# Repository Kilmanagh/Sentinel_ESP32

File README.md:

# Sentinel ESP32

Sentinel is an ESP32-based multi-sensor node built around ESPHome and Home Assistant.

The active implementation lives in `esphome/sentinel.yaml`. The old PlatformIO project in `pio-ARCHIVE/` is deprecated and is no longer the source of truth.

## Current firmware

- Active config: `esphome/sentinel.yaml`
- Secrets file: `esphome/secrets.yaml`
- Board target: `esp32dev`
- Framework: ESPHome on Arduino
- Home Assistant integration: native ESPHome API
- Device services: Wi-Fi, OTA, web server, local fallback AP, and Home Assistant entity-based runtime tuning

## Features

- BME280 environment telemetry
- AM312 PIR motion detection with warmup, stable-detect, stable-clear, and hold timing
- MAX9814 sound intrusion detection using peak-to-peak sampling
- Reed switch door state reporting
- Sound-level calibration helpers and approximate dB display
- Smoke alarm tone and cadence detection
- Device-health diagnostics and fault indicators
- Three-pixel WS2812 status LED strip plus onboard status LED
- Runtime tuning through Home Assistant entities exposed by ESPHome

## Primary docs

- `docs/Adjustments.MD` - active ESPHome tuning, calibration, and sensor-behavior guide
- `docs/Hardware_Deliverables.md` - current hardware, pin mapping, and LED wiring summary
- `hardware/Sentinel_Baseplate_Kit_Wiring.md` - practical baseplate / Dupont wiring guide for the actual 30-pin ESP32 board and expansion kit
- `hardware/Sentinel_Baseplate_Kit_Wiring.md` also includes a Sentinel-only pin map and a first bring-up checklist for bench validation
- `docs/Sentinel_Home_Assistant_Helpers.md` - optional Home Assistant helper package for counters, mode helpers, and last-event tracking
- `docs/Sentinel_Lovelace_Dashboard.md` - dashboard layout, setup, and troubleshooting view
- `docs/Sentinel_Lovelace_Dashboard.yaml` - Lovelace YAML for the dashboard itself

## Deploy

Use ESPHome to validate and install `esphome/sentinel.yaml`.

Typical workflow:

1. Fill in `esphome/secrets.yaml` with your Wi-Fi credentials.
2. Open `esphome/sentinel.yaml` in ESPHome or the Home Assistant ESPHome add-on.
3. Validate the config.
4. Install over USB for first flash, then use OTA afterward if desired.

## Notes

- The active docs no longer use the old MQTT, serial `cfg`, or BLE watchlist workflow.
- If you need historical PlatformIO material, keep it isolated under `pio-ARCHIVE/`.

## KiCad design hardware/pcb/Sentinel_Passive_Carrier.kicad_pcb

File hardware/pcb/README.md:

# PCB Package

This directory holds PCB fabrication package assets.

## Current recommendation

For the current Sentinel hardware build, do not treat this folder as the primary assembly path.

The recommended real-world build is:

- the existing AITRIP ESP32 baseplate / expansion kit
- Dupont wiring
- the practical wiring guide in `hardware/Sentinel_Baseplate_Kit_Wiring.md`

This `hardware/pcb/` folder should currently be treated as an experimental custom-board branch and documentation artifact, not the default build path.

## Current source

- `Sentinel_Passive_Carrier.kicad_pcb`: generated KiCad board source for a passive carrier board
- `generate_passive_carrier.py`: reproducible pcbnew generator for the current board source
- `Sentinel_Passive_Carrier_drc.rpt`: latest KiCad DRC report

## Current design scope

This is a passive carrier board derived from the current wiring, schematic, and enclosure documentation.

It assumes:

- ESP32 DevKit remains off-board and connects through a wire harness header rather than a direct socket footprint
- BME280, AM312, MAX9814, reed switch, and LED strip land on generic header / terminal positions
- board outline is sized conservatively to fit within the current 95 mm x 65 mm enclosure envelope

It is useful for:

- preserving the custom PCB experiment
- future routing / layout work
- exporting fabrication files for review while the design is still being corrected

It is not yet the recommended path for:

- immediate hardware assembly
- ordering production boards
- using as the single source of truth for the active build

## Fabrication package

The `gerbers/` folder now contains real KiCad exports for the passive carrier board, including:

- copper layers
- solder mask layers
- silkscreen layers
- edge cuts
- Excellon drill file
- drill map and drill report
- KiCad gerber job file

## Validation status

The fabrication package is generated from a real board source, but the current carrier layout is not yet fully DRC-clean.

Practical meaning:

- the files are real KiCad exports
- the board is still not ready to be treated as fabrication-safe
- the DRC report must be resolved before any board order is placed

Until that happens, the active hardware reference remains the baseplate / Dupont path documented in `hardware/Sentinel_Baseplate_Kit_Wiring.md`.

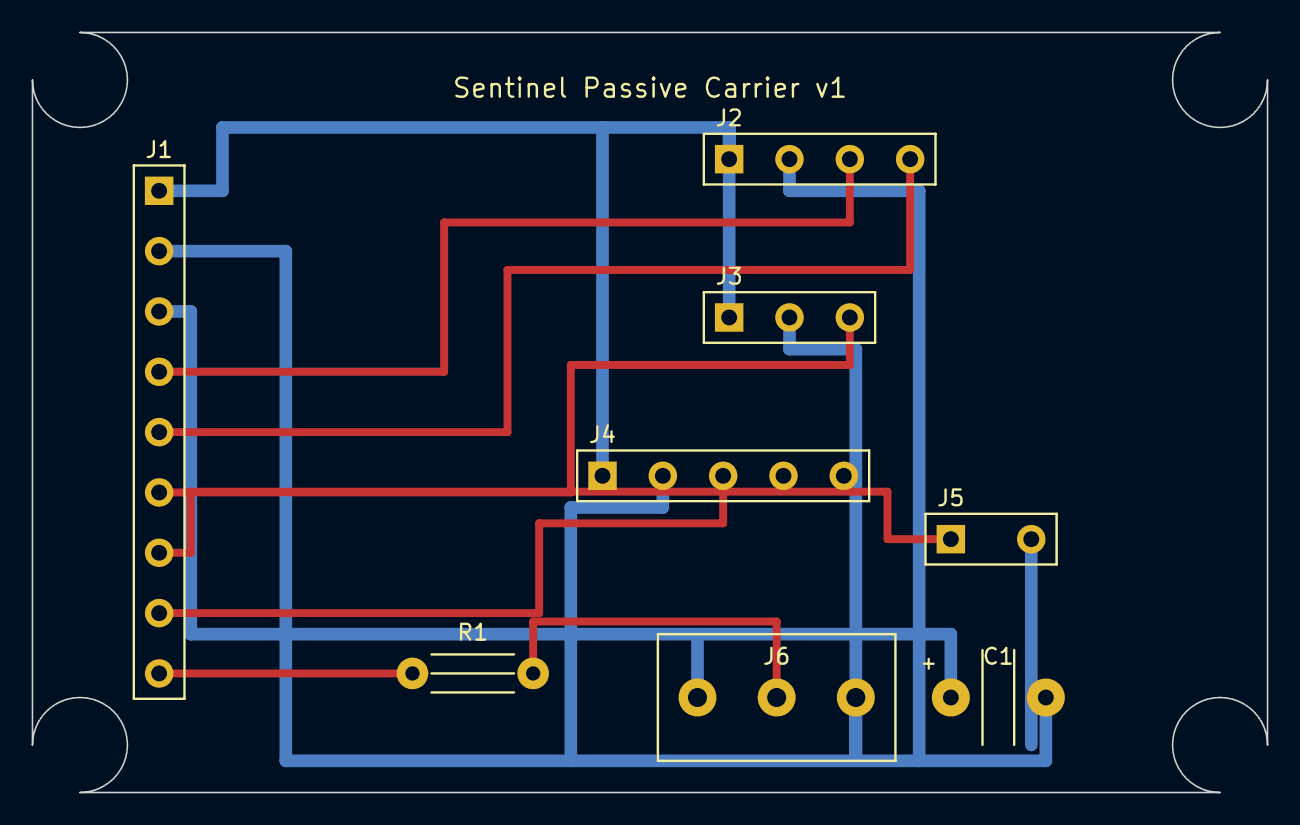
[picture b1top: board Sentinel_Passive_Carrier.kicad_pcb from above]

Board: 2 copper layers, 78.0 x 48.0 mm, 8 parts (0 on the bottom side), 10 nets.

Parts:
C1: 470uF
J1: ESP32_WIRE_HARNESS
J2: BME280
J3: AM312_PIR
J4: MAX9814
J5: REED_SWITCH
J6: LED_STRIP
R1: 330R

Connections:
3V3: J1.1, J2.1, J3.1, J4.1
5V_LED: C1.1, J1.3, J6.1
GND: C1.2, J1.2, J2.2, J3.2, J4.2, J5.2, J6.3
I2C_SCL: J1.5, J2.4
I2C_SDA: J1.4, J2.3
LED_DATA: J1.9, R1.1
LED_DATA_IN: J6.2, R1.2
MIC_ANALOG: J1.8, J4.3
PIR_DATA: J1.6, J3.3
REED_SIGNAL: J1.7, J5.1

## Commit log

2026-05-13 Initial plan
2026-05-13 feat: add sentinel esp32 node firmware and hardware/doc scaffolding
    Agent-Logs-Url: https://github.com/Kilmanagh/Sentinel_ESP32/sessions/5bc2e0f3-658e-4ccc-94b3-6b78b24097ab
2026-05-13 refactor: deduplicate sensor conversion and clarify interval checks
    Agent-Logs-Url: https://github.com/Kilmanagh/Sentinel_ESP32/sessions/5bc2e0f3-658e-4ccc-94b3-6b78b24097ab
2026-05-13 fix: align sensor sampling timing and shared readings
    Agent-Logs-Url: https://github.com/Kilmanagh/Sentinel_ESP32/sessions/5bc2e0f3-658e-4ccc-94b3-6b78b24097ab
2026-05-13 perf: sample ADC only when telemetry or heartbeat is due
    Agent-Logs-Url: https://github.com/Kilmanagh/Sentinel_ESP32/sessions/5bc2e0f3-658e-4ccc-94b3-6b78b24097ab
2026-05-13 Upgrade Sentinel ESP32 Node to firmware v2.0
    Updated the Sentinel ESP32 Node firmware to version 2.0, adding features for environmental monitoring, security, and diagnostics.
2026-05-13 Enhance Hardware Deliverables documentation
    Expanded documentation to include detailed hardware components, wiring configurations, and firmware logic adjustments for the Sentinel ESP32 Node.
2026-05-13 Refactor comments and update door state logic
2026-05-13 Add platformio.ini configuration for ESP32 project
2026-05-13 Rename Sentinel_ESP32_Node.ino to src/Sentinel_ESP32_Node.ino
2026-05-13 Rename platformio.ini to src/platformio.ini
2026-05-13 Revise hardware deliverables and wiring notes
    Updated hardware configuration details and added wiring connection notes for clarity.
2026-05-13 Add MQTT Topic Map for Sentinel ESP32 Node
    This document outlines the MQTT topics and JSON payloads used by the Sentinel ESP32 Node for communication with Home Assistant, detailing the structure and frequency of various sensor data.
2026-05-13 Fix formatting in MQTT Topic Map documentation
2026-05-13 Document wiring and specifications for Sentinel ESP32 Node
    Added detailed wiring and component specifications for the Sentinel ESP32 Node, including power distribution and sensor connections.
2026-05-13 Add Netlist schematic for hardware components
2026-05-13 Add complete documentation for Sentinel ESP32 project
    This document provides comprehensive technical specifications, hardware deliverables, MQTT topic maps, and calibration guides for the Sentinel ESP32 Multi-Sensor Node.
2026-05-13 Add Sentinel ESP32 enclosure specifications document
    This document outlines the specifications for the 3D-printed enclosure of the Sentinel ESP32 Node, including physical dimensions, sensor integration requirements, and recommended print settings.
2026-05-13 Add OpenSCAD model for ESP32 Node Enclosure
2026-05-13 Revise assembly and disassembly instructions
    Updated section numbers and added detailed assembly and disassembly instructions for the Sentinel Enclosure.
2026-05-13 Rename Sentinel_Enclosure to Sentinel_Enclosure.md
2026-05-13 Add wiring guide for Sentinel Multi-Sensor Node
    This document provides a comprehensive wiring guide for the Sentinel Multi-Sensor Node, detailing power and ground connections, component pin mappings, and a wiring master table.
2026-05-13 Update Sentinel ESP32 Node Enclosure design
2026-05-13 Modify library dependencies and build flags
    Updated library dependencies and build flags in platformio.ini.
2026-05-15 Rename src/platformio.ini to platformio.ini
2026-05-15 Add initial implementation of Sentinel Firmware v2.0 for ESP32 multi-sensor monitor
    - Created main application file (main.cpp) with features including environmental monitoring, motion detection, sound intrusion detection, and BLE scanning.
    - Added configuration for WiFi and MQTT connectivity.
    - Implemented Home Assistant auto-discovery for sensor integration.
    - Introduced diagnostics for system health monitoring.
    - Added .gitignore file to exclude build artifacts and IDE configurations.
    - Included VSCode extensions recommendations for development environment setup.
2026-05-15 Add .gitignore and extensions.json for VSCode configuration
2026-05-15 Add board_build.partitions configuration to platformio.ini
2026-05-15 Refactor WiFi and time synchronization handling; load credentials from secrets.h if available
2026-05-15 Add runtime configuration management using Preferences for WiFi and MQTT settings
2026-05-15 Implement runtime configuration management with serial command handling
2026-05-15 Update serial command help message to include 'cfg list' option
2026-05-15 Improve serial command handling to process non-empty lines only
2026-05-16 Enhance PIR motion detection logic with warmup and stability checks
2026-05-16 Implement BLE device tracking and presence publishing with scan management
2026-05-16 Add BLE presence publishing during MQTT connection setup
2026-05-16 Increase MQTT buffer size and add publish failure logging
2026-05-16 Add BLE active device summary and publish list during presence updates
2026-05-16 Add configurable parameters for PIR motion detection timing
2026-05-16 Add PIR configuration discovery and state publishing via MQTT
2026-05-16 Add sound sensor configuration and state management via MQTT
2026-05-16 Refactor BLE functionality to implement beacon watchlist
    - Updated BLE scanning to focus on a fixed-size watchlist for beacons.
    - Replaced BLE device tracking with beacon-specific structures and logic.
    - Introduced new configuration options for beacon names, UUIDs, majors, and minors.
    - Enhanced MQTT discovery and state publishing for beacons.
    - Removed legacy BLE device handling and associated topics.
    - Improved UUID normalization and validation for beacons.
2026-05-16 Enhance documentation and add BLE enrollment logging commands
2026-05-18 Add initial ESPHome configuration for Sentinel node with PIR and sound detection
2026-05-19 Add throttle filter to ADC template sensors and set logger level to INFO
2026-05-20 Refactor Wi-Fi configuration to use secrets file for SSID and password
2026-05-20 Add switches to enable/disable PIR and sound detection with state restoration
2026-05-20 Refactor sensor and switch names to remove friendly name prefix for clarity; add Comfort Index and IAQ Score sensors.
2026-05-20 Add web server configuration to ESPHome for Sentinel node
2026-05-20 Add sound level calibration parameters and calculations for ESPHome trial
2026-05-20 Add OTA platform configuration for ESPHome
2026-05-20 Add reset_runtime_states script and button to initialize detection states
2026-05-20 Refactor Sentinel node configuration: update device names and comments for clarity
2026-05-20 Add smoke alarm sensing features: implement detection parameters and configuration options
2026-05-20 Refactor smoke alarm state initialization: streamline variable assignments and formatting
2026-05-20 Add smoke alarm beep count and last beep age sensors: enhance detection metrics for improved monitoring
2026-05-20 Clarify sound detection parameters: distinguish between sound threshold and level scaling for improved user understanding
2026-05-20 Add sound calibration features: implement capture duration, baseline, and reference settings for improved sound detection
2026-05-20 Remove entity_category from template switches and buttons for cleaner configuration
2026-05-20 Add Sentinel Lovelace Dashboard documentation: provide installation steps, layout overview, and troubleshooting guidance for improved user experience
2026-05-21 Add smoke alarm customization options: implement profiles and custom tone settings for enhanced detection flexibility
2026-05-21 Add device health diagnostics: implement WiFi and API connection states, boot count, and memory metrics for improved monitoring
2026-05-21 Fix smoke profile retrieval: use current_option() for default value fallback
2026-05-21 Add status pixel feature: implement visual state feedback with customizable effects
2026-05-21 Fix smoke profile retrieval: ensure default value is set when current option is empty
2026-05-21 Enhance status LED functionality: implement multiple LEDs for system health, activity, and alerts with new controls and troubleshooting options
2026-05-21 Add switches for PIR, sound, and smoke alarm sensing; enhance status LED configuration
2026-05-21 Enhance wiring documentation: add detailed information for WS2812 LED chain, including power, ground, and data connections
2026-05-21 Add status LED meaning sensors: implement left, center, and right LED meaning indicators for enhanced diagnostics
2026-05-21 Refactor status LED entity types: update to use sensor entities for LED meanings and clean up unnecessary whitespace in the dashboard YAML
2026-05-21 Add Home Assistant helpers package and update documentation: include event counters, last-event tracking, and mode selector for enhanced integration
2026-05-21 Refactor code structure for improved readability and maintainability
2026-05-21 Refactor documentation and archive legacy files
    - Deleted outdated `Sentinel_ESP32_Node.md` and `Sentinel_Full_Project_Reference.md` files.
    - Created new `Adjustments.MD` to provide detailed sensor adjustment guidelines.
    - Added `MQTT_Topic_Map.md` to outline MQTT topics and payload structures for Home Assistant integration.
    - Archived previous versions of `Sentinel_ESP32_Node.md` and `Sentinel_Full_Project_Reference.md` for historical reference.
2026-05-21 Update README and remove legacy project reference for clarity and accuracy
2026-05-22 Add Sentinel ESP32 Enclosure documentation and specifications
    - Created Sentinel_Enclosure.md for assembly, installation, and service notes for the v2_7 enclosure layout.
    - Added Sentinel_Enclosure_Guide.stl for a simplified geometric representation of the enclosure.
    - Introduced Sentinel_Enclosure_Specs.md detailing the mechanical design, dimensions, and features of the v2_7 enclosure.
2026-05-22 Add schematic files and BOM for Sentinel ESP32 Node
    - Created ERC report for Sentinel ESP32 Node schematic, highlighting symbol mismatches and library issues.
    - Added netlist file for Sentinel ESP32 Node, detailing components and connections.
    - Introduced a Bill of Materials (BOM) and connection landing table for the Sentinel ESP32 Node, outlining component specifications and wiring details.
2026-05-22 Add baseplate wiring guide and update related documentation for AITRIP ESP32 integration
